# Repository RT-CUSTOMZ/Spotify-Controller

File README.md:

# Spotify-Controller
Für mehr Details schaut bitte ins [Wiki](https://github.com/RT-CUSTOMZ/Spotify-Controller/wiki).

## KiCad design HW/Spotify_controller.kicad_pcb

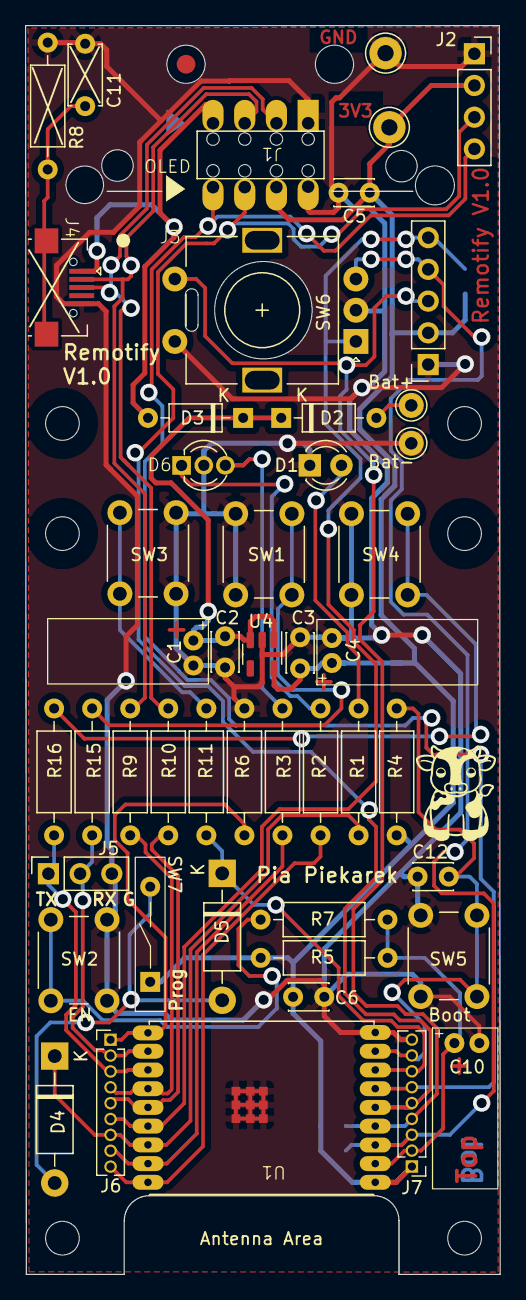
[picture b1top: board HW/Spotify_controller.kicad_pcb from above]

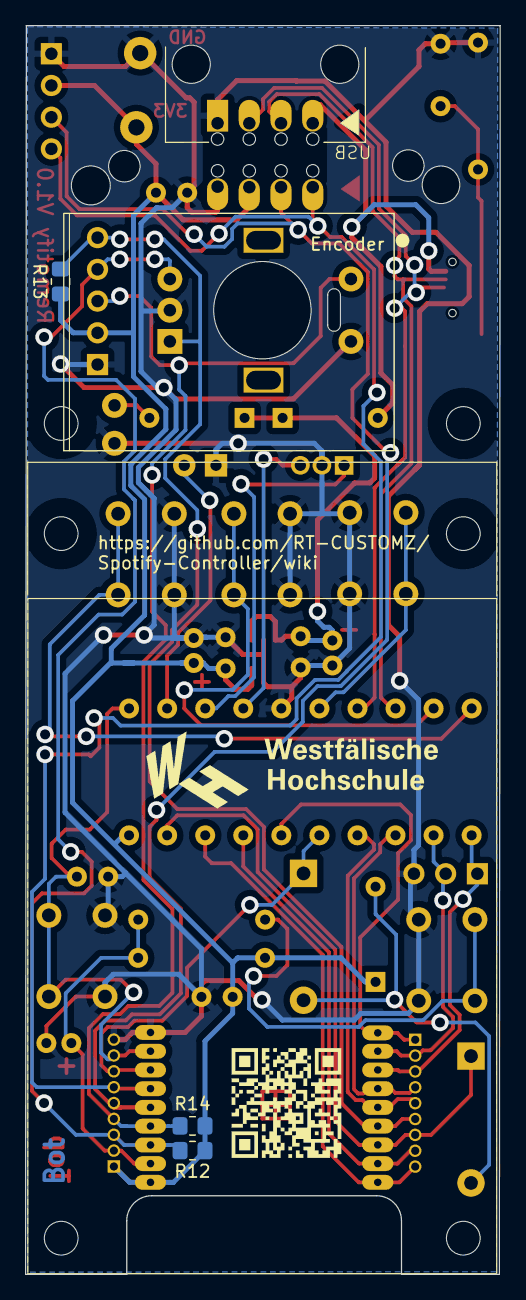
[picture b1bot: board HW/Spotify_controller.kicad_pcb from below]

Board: 2 copper layers, 38.0 x 100.0 mm, 61 parts (6 on the bottom side), 32 nets.

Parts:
BT1: Battery_Holder; Battery_holder
C1, C4, C10: 1u; C_Radial_D5.0mm_H11.0mm_P2.00mm_liegend
C2, C3, C5, C6, C12: 100n; C_Disc_D3.0mm_W2.0mm_P2.50mm
C11: 4n7; C_Disc_D4.7mm_W2.5mm_P5.00mm
D1: LED; LED_D3.0mm
D2, D3: 1N4148; D_DO-35_SOD27_P7.62mm_Horizontal
D4, D5: 1N5819; D_DO-41_SOD81_P10.16mm_Horizontal
D6: Zweifarb-LED; LED-3Pin
FID1, FID2, FID3: Fiducial; Fiducial_1.5mm_Mask3mm
H1, H2, H3, H4, H5, H6: MountingHole; MountingHole_2.7mm_M2.5
J1: Conn_02x04_Top_Bottom; USB_C_and_Oled
J2: Conn_01x04; PinSocket_1x04_P2.54mm_Vertical
J3: Conn_01x05_Socket; Encoder KY-040
J4: USB_B_Micro; USB_B_Micro_CN
J5: Conn_01x03; PinSocket_1x03_P2.54mm_Vertical
J6, J7: Conn_01x09_Pin; PinHeader_1x09_P1.27mm_Vertical
R1, R11, R15, R16: 300R; R_Axial_DIN0207_L6.3mm_D2.5mm_P10.16mm_Horizontal
R2, R3: 100R; R_Axial_DIN0207_L6.3mm_D2.5mm_P10.16mm_Horizontal
R4, R5: 10k; R_Axial_DIN0207_L6.3mm_D2.5mm_P10.16mm_Horizontal
R6: 10K; R_Axial_DIN0207_L6.3mm_D2.5mm_P10.16mm_Horizontal
R7, R9, R10: 22R; R_Axial_DIN0207_L6.3mm_D2.5mm_P10.16mm_Horizontal
R8: 1M; R_Axial_DIN0207_L6.3mm_D2.5mm_P10.16mm_Horizontal
R12, R13, R14: 10k; R_0805_2012Metric_Pad1.20x1.40mm_HandSolder
SW1, SW3, SW4: SW_Push; SW_PUSH_6mm_H7.3mm
SW2: SW_Push; SW_PUSH_6mm_H4.3mm
SW5: Boot; SW_PUSH_6mm_H4.3mm
SW6: RotaryEncoder_Switch; RotaryEncoder_Alps_EC11E-Switch_Vertical_H20mm
SW7: SW_DIP_x01; Drahtschalter
TP1: Bat+; Pin_D1.0mm_L10.0mm
TP2: Bat-; Pin_D1.0mm_L10.0mm
TP3: GND; Pin_D1.3mm_L11.0mm
TP4: 3V3; Pin_D1.3mm_L11.0mm
U1: ESP32-C3-WROOM-02; ESP32_C3_Wroom_02-easysolder
U4: AP2112K-3.3; SOT-23-5

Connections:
+3V3: C3.1, C4.1, C5.2, C6.1, J1.6, J2.2, J3.2, J7.1, R4.1, R5.1, R12.1, R13.1, R14.1, SW7.1, TP4.1, U1.1 (3V3), U4.5 (VOUT)
/5V_IN: C1.1, C2.1, D2.1 (K), D3.1 (K), U4.1 (VIN), U4.3 (EN)
/Boot: C12.2, J7.8, R4.2, SW5.1, U1.8 (GPIO9)
/Button_Left: D5.1 (K), J7.7, R11.1, U1.7 (GPIO8)
/D+: J1.2, J4.3 (D+), R10.1
/D-: J1.3, J4.2 (D-), R9.1
/DUOLED_1: J6.9, R2.1, U1.18 (GPIO0/ADC1_CH0/XTAL_32K_P)
/DUOLED_2: J6.8, R3.1, U1.17 (GPIO1/ADC1_CH1/XTAL_32K_N)
/EN: C10.1, J7.2, R5.2, R7.1, U1.2 (EN/CHIP_PU)
/GPIO2/LED: D4.1 (K), J6.7, R1.1, U1.16 (GPIO2/ADC1_CH2)
/GPIO10: J6.1, R6.1, U1.10 (GPIO10)
/Program1: D4.2 (A), D5.2 (A), SW7.2
/RX/Button_Middle: J5.2, J6.2, R15.2, U1.11 (GPIO20/U0RXD)
/TX/Button_Right: J5.1, J6.3, R16.2, U1.12 (GPIO21/U0TXD)
/USR_BTN_LEFT: R11.2, SW3.1
/VCC_{BAT}: D2.2 (A), TP1.1
CLK/SCL: J1.7, J2.3, J7.5, U1.5 (GPIO6)
ENC_CLK: J3.5, J6.6, R13.2, SW6.A, U1.15 (GPIO3/ADC1_CH3)
ENC_DT: J3.4, J7.3, R12.2, SW6.B, U1.3 (GPIO4/ADC1_CH4)
ENC_SW: J3.3, J7.4, R14.2, SW6.S1, U1.4 (GPIO5/ADC2_CH0)
GND: C1.2, C2.2, C3.2, C4.2, C5.1, C6.2, C10.2, C11.1, C12.1, D1.1 (K), D6.2 (K), J1.1, J1.5, J2.1, J3.1, J4.5 (GND), J5.3, J7.9, R6.2, R8.2, SW1.2, SW2.2, SW3.2, SW4.2, SW5.2, SW6.C, SW6.S2, TP2.1, TP3.1, U1.9 (GND), U1.19 (GND), U4.2 (GND)
MOSI/SDA: J1.8, J2.4, J7.6, U1.6 (GPIO7)
unnamed: D1.2 (A), R1.2
unnamed: D6.1 (A), R2.2
unnamed: D6.3 (A), R3.2
unnamed: C11.2, J4.6 (Shield), R8.1
unnamed: R7.2, SW2.1
USB_DN: J6.4, R9.2, U1.13 (GPIO18/USB_D-)
USB_DP: J6.5, R10.2, U1.14 (GPIO19/USB_D+)
USR_BTN_MIDDLE: R15.1, SW1.1
USR_BTN_RIGHT: R16.1, SW4.1
VBUS: D3.2 (A), J1.4, J4.1 (VBUS)

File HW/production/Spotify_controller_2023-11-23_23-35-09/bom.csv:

Designator,Footprint,Quantity,Value,LCSC Part #
3V3,Pin_D1.3mm_L11.0mm,1,3V3,
BT1,Battery_holder,1,Battery_Holder,
"C1, C10, C4",C_Radial_D5.0mm_H11.0mm_P2.00mm_liegend,3,1u,
C11,C_Disc_D4.7mm_W2.5mm_P5.00mm,1,4n7,DNP
"C12, C2, C3, C5, C6",C_Disc_D3.0mm_W2.0mm_P2.50mm,5,100n,
D1,LED_D3.0mm,1,LED,
"D2, D3",D_DO-35_SOD27_P7.62mm_Horizontal,2,1N4148,
"D4, D5",D_DO-41_SOD81_P7.62mm_Horizontal,2,1N5819,
D6,LED_D3.0mm-3,1,~,
GND1,Pin_D1.3mm_L11.0mm,1,GND,
J1,USB_C_and_Oled,1,Conn_02x04_Top_Bottom,
J3,Encoder KY-040,1,Conn_01x05_Socket,
J4,USB_B_Micro_CN,1,USB_B_Micro,DNP
J5,PinSocket_1x03_P2.54mm_Vertical,1,Conn_01x03,
"J6, J7",PinHeader_1x09_P1.27mm_Vertical,2,Conn_01x09_Pin,
"R1, R11, R15, R16",R_Axial_DIN0207_L6.3mm_D2.5mm_P10.16mm_Horizontal,4,300R,
"R10, R7, R9",R_Axial_DIN0207_L6.3mm_D2.5mm_P10.16mm_Horizontal,3,22R,
"R12, R13, R14",0805,3,10k,
"R2, R3",R_Axial_DIN0207_L6.3mm_D2.5mm_P10.16mm_Horizontal,2,100R,
"R4, R5, R6",R_Axial_DIN0207_L6.3mm_D2.5mm_P10.16mm_Horizontal,3,10k,
R8,R_Axial_DIN0207_L6.3mm_D2.5mm_P10.16mm_Horizontal,1,1M,DNP
"SW1, SW3, SW4",SW_PUSH_6mm_H7.3mm,3,SW_Push,
SW2,SW_PUSH_6mm_H4.3mm,1,SW_Push,
SW5,SW_PUSH_6mm_H4.3mm,1,Boot,
SW6,RotaryEncoder_Alps_EC11E-Switch_Vertical_H20mm,1,RotaryEncoder_Switch,
SW7,Drahtschalter,1,SW_DIP_x01,
TP1,Pin_D1.0mm_L10.0mm,1,Bat+,
TP2,Pin_D1.0mm_L10.0mm,1,Bat-,
U1,ESP32_C3_Wroom_02-easysolder,1,ESP32-C3-WROOM-02,
U4,SOT-23-5,1,AP2112K-3.3,

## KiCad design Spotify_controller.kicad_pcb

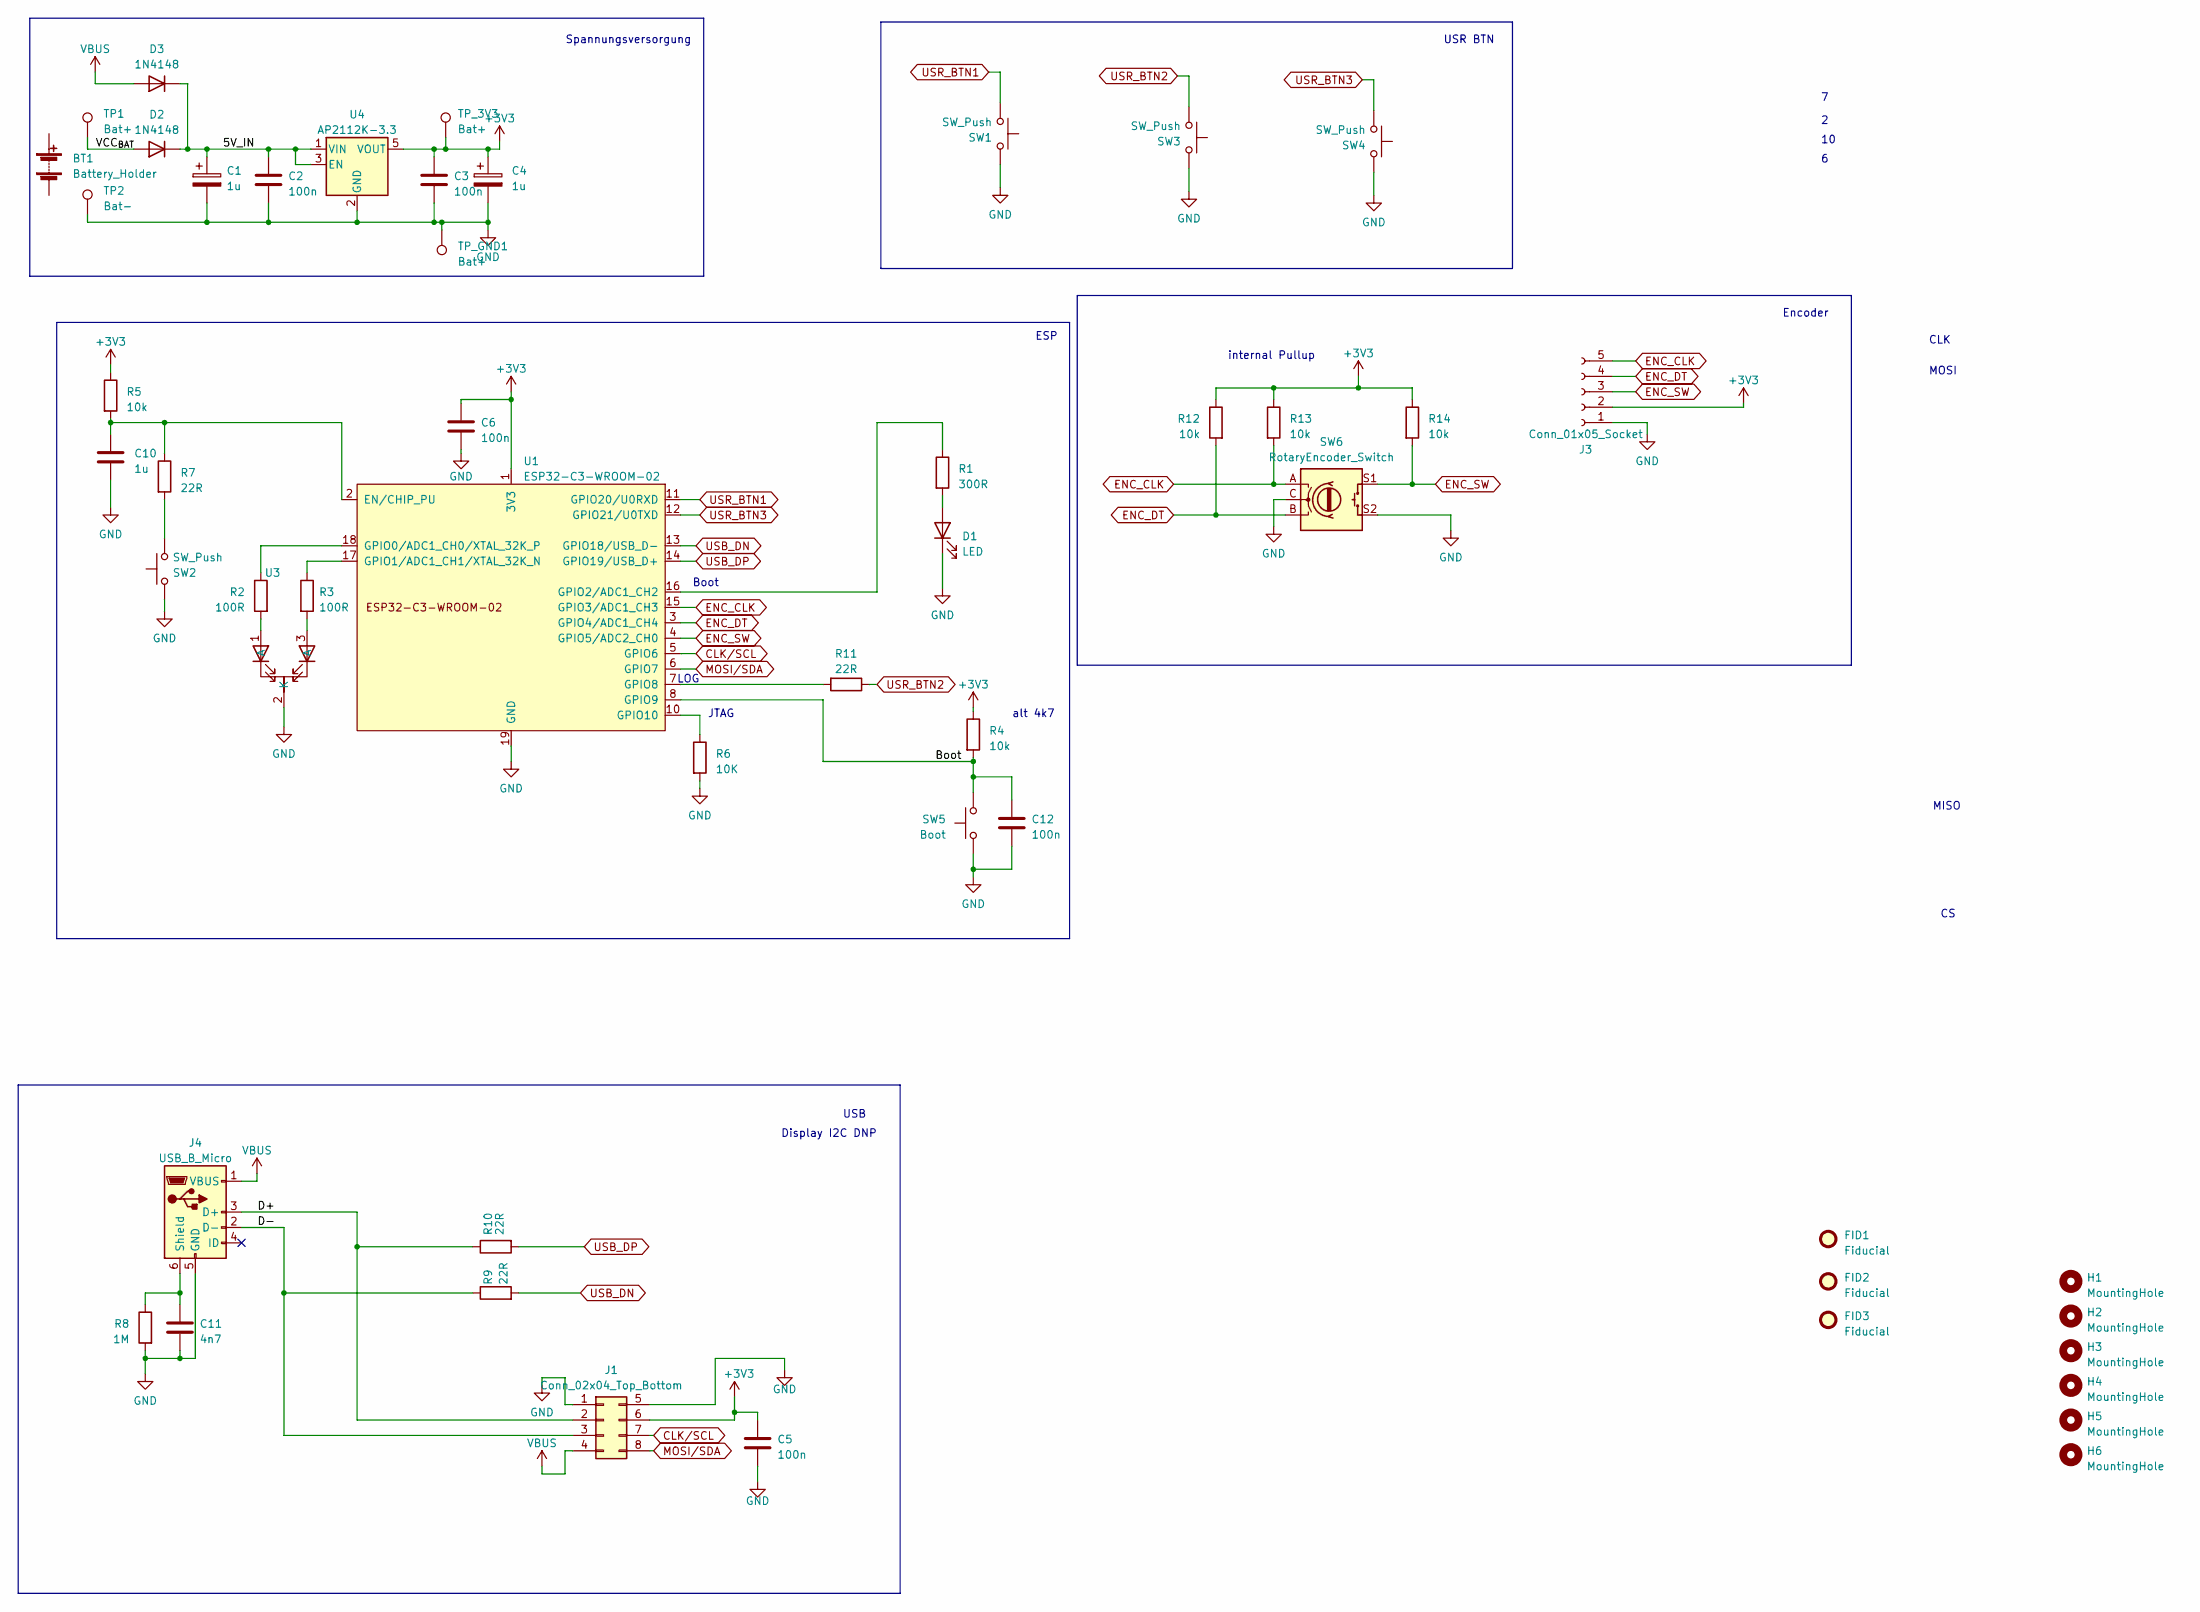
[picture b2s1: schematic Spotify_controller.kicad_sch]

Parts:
BT1: Battery_Holder; Battery_holder
C1, C4, C10: 1u; C_Radial_D5.0mm_H11.0mm_P2.00mm_liegend
C2, C3, C5, C6, C12: 100n; C_Disc_D3.0mm_W2.0mm_P2.50mm
C11: 4n7; C_Disc_D3.0mm_W2.0mm_P2.50mm
D1: LED; LED_D3.0mm
D2, D3: 1N4148; D_DO-35_SOD27_P7.62mm_Horizontal
FID1, FID2, FID3: Fiducial; Fiducial_1.5mm_Mask3mm
H1, H2, H3, H4, H5, H6: MountingHole; MountingHole_2.7mm_M2.5
J1: Conn_02x04_Top_Bottom; USB_C_and_Oled
J3: Conn_01x05_Socket; Encoder KY-040
J4: USB_B_Micro; USB_B_Micro_CN
R1: 300R; R_Axial_DIN0207_L6.3mm_D2.5mm_P10.16mm_Horizontal
R2, R3: 100R; R_Axial_DIN0207_L6.3mm_D2.5mm_P10.16mm_Horizontal
R4, R5: 10k; R_Axial_DIN0207_L6.3mm_D2.5mm_P10.16mm_Horizontal
R6: 10K; R_Axial_DIN0207_L6.3mm_D2.5mm_P10.16mm_Horizontal
R7, R9, R10, R11: 22R; R_Axial_DIN0207_L6.3mm_D2.5mm_P10.16mm_Horizontal
R8: 1M; R_Axial_DIN0207_L6.3mm_D2.5mm_P10.16mm_Horizontal
R12, R13, R14: 10k; R_0805_2012Metric_Pad1.20x1.40mm_HandSolder
SW1, SW3, SW4: SW_Push; SW_PUSH_6mm_H7.3mm
SW2: SW_Push; SW_PUSH_6mm_H4.3mm
SW5: Boot; SW_PUSH_6mm_H4.3mm
SW6: RotaryEncoder_Switch; RotaryEncoder_Alps_EC11E-Switch_Vertical_H20mm
TP1: Bat+; Pin_D1.0mm_L10.0mm
TP2: Bat-; Pin_D1.0mm_L10.0mm
TP_3V3: Bat+; Pin_D1.0mm_L10.0mm
TP_GND1: Bat+; Pin_D1.0mm_L10.0mm
U1: ESP32-C3-WROOM-02; ESP32_C3_Wroom_02-easysolder
U3: LED_D3.0mm-3
U4: AP2112K-3.3; SOT-23-5

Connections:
+3V3: C3.1, C4.1, C5.2, C6.1, J1.6, J3.2, R4.1, R5.1, R12.1, R13.1, R14.1, TP_3V3.1, U1.1 (3V3), U4.5 (VOUT)
/5V_IN: C1.1, C2.1, D2.1 (K), D3.1 (K), U4.1 (VIN), U4.3 (EN)
/Boot: C12.2, R4.2, SW5.1, U1.8 (GPIO9)
/D+: J1.2, J4.3 (D+), R10.1
/D-: J1.3, J4.2 (D-), R9.1
/VCC_{BAT}: D2.2 (A), TP1.1
CLK/SCL: J1.7, U1.5 (GPIO6)
ENC_CLK: J3.5, R13.2, SW6.A, U1.15 (GPIO3/ADC1_CH3)
ENC_DT: J3.4, R12.2, SW6.B, U1.3 (GPIO4/ADC1_CH4)
ENC_SW: J3.3, R14.2, SW6.S1, U1.4 (GPIO5/ADC2_CH0)
GND: C1.2, C2.2, C3.2, C4.2, C5.1, C6.2, C10.1, C11.1, C12.1, D1.1 (K), J1.1, J1.5, J3.1, J4.5 (GND), R6.2, R8.2, SW1.2, SW2.2, SW3.2, SW4.2, SW5.2, SW6.C, SW6.S2, TP2.1, TP_GND1.1, U1.9 (GND), U1.19 (GND), U3.2 (K), U4.2 (GND)
MOSI/SDA: J1.8, U1.6 (GPIO7)
unnamed: D1.2 (A), R1.2
unnamed: C11.2, J4.6 (Shield), R8.1
unnamed: R2.2, U3.1 (A)
unnamed: R3.2, U3.3 (A)
unnamed: R7.2, SW2.1
unnamed: C10.2, R5.2, R7.1, U1.2 (EN/CHIP_PU)
unnamed: R2.1, U1.18 (GPIO0/ADC1_CH0/XTAL_32K_P)
unnamed: R3.1, U1.17 (GPIO1/ADC1_CH1/XTAL_32K_N)
unnamed: R1.1, U1.16 (GPIO2/ADC1_CH2)
unnamed: R11.2, U1.7 (GPIO8)
unnamed: R6.1, U1.10 (GPIO10)
USB_DN: R9.2, U1.13 (GPIO18/USB_D-)
USB_DP: R10.2, U1.14 (GPIO19/USB_D+)
USR_BTN1: SW1.1, U1.11 (GPIO20/U0RXD)
USR_BTN2: R11.1, SW3.1
USR_BTN3: SW4.1, U1.12 (GPIO21/U0TXD)
VBUS: D3.2 (A), J1.4, J4.1 (VBUS)

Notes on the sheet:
alt 4k7
JTAG
USB
CLK
USR BTN
Encoder
ESP
internal Pullup
MOSI
Spannungsversorgung
MISO
Boot
Display I2C DNP
LOG

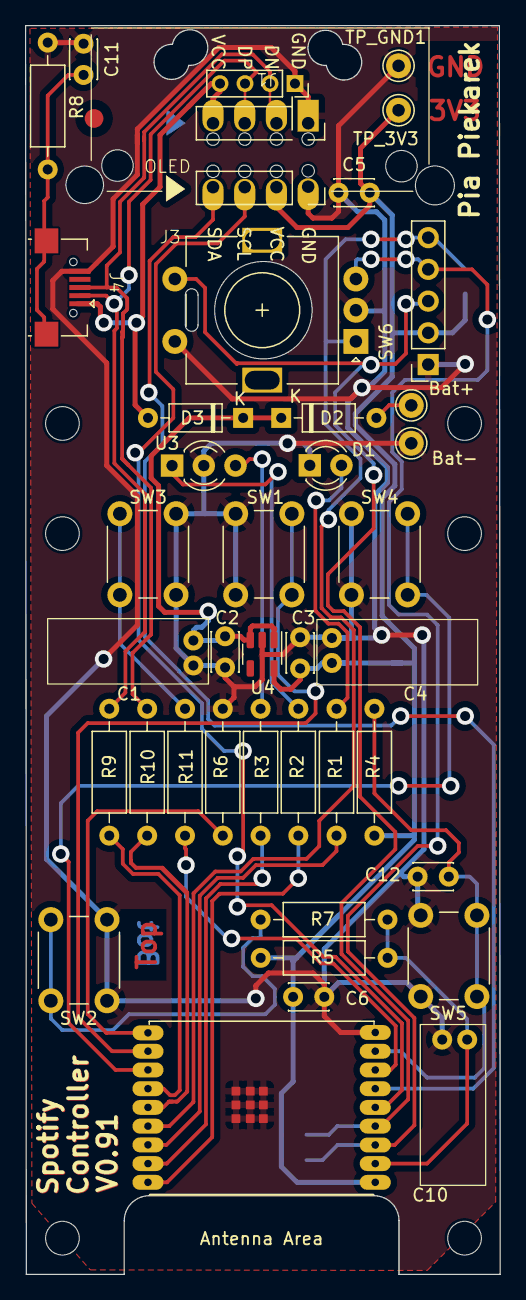
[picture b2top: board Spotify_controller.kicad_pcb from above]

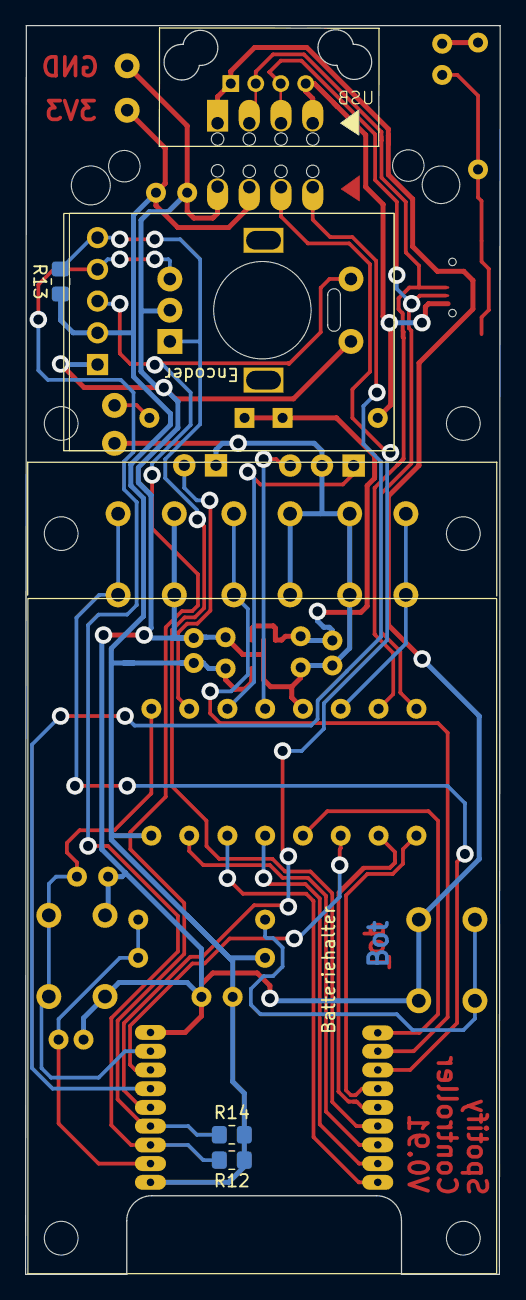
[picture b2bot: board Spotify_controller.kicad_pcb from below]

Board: 2 copper layers, 38.0 x 100.0 mm, 52 parts (6 on the bottom side), 29 nets.

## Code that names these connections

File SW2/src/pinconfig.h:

#pragma once
#include "Arduino.h"
/**************************************
    Do not change anything in this File
**************************************/

//Single Red LED
const uint8_t led_red_pin = 2; 

//Tri-Color LED
const uint8_t led_orange = 0;
const uint8_t led_green = 1;

//User Buttons
const uint8_t button_left = 8;
const uint8_t button_middle = 20;
const uint8_t button_right = 21;


//Display Pins
const uint8_t display_sda = 7;
const uint8_t display_scl = 6;

//USB Pins
const uint8_t usb_dn = 18;
const uint8_t usb_dp = 19;

//Encoder Pins
const uint8_t encoder_clk = 3;
const uint8_t encoder_dt = 4;
const uint8_t encoder_sw = 5;

void init_pins();

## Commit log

2023-11-17 add gitignore
2023-11-17 add V0.91
2023-11-18 add latest changes
2023-11-18 add HW Folder
2023-11-23 add hw bugfixes
2023-11-25 add all current changes
2023-11-25 rename SW3 to SW
2023-11-25 further restructuring of repo
2023-11-25 working button
2023-11-25 add interrupt handling
2023-11-25 Manufacturing Data for JLCPCB generated
2023-11-25 modify state machine and fix Button Bug
2023-11-25 add documentation to the buttons
2023-11-28 add minor changes to Schematic and PCB
2023-11-29 clean main.h
2023-11-29 Separate SPIFFS from WifiManager
2023-11-29 add minor change to test kibot workflow
2023-11-30 add minor changes
2023-11-30 additional minor changes
2023-11-30 minor changes 2
2023-12-25 add several changes to HW and SW
2023-12-25 add changes
2024-01-01 add software changes for encoder/volume and others
2024-01-01 changes to make display work
2024-01-04 add changes to repo
2024-01-05 change encoder etc
2024-01-05 add minor changes to display etc
2024-01-05 remove most of the things for explanation
